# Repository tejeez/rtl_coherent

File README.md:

rtl_coherent: Synchronized RTL-SDR receivers
============================================

This is a hardware and software project to synchronize multiple RTL-SDR
receivers and make it possible to use them for applications such as
radio direction finding, passive radars, measuring equipment,
radio astronomy interferometers and MIMO communications.

Basic idea
----------

A single 28.8 MHz reference clock is distributed to all dongles. This makes
their sampling rates and local oscillator frequencies equal but doesn't
guarantee that they would actually sample simultaneously or that their
local oscillators would be in the same phase. 

Both the local oscillator phase and sample time offset get a random value
every time the dongles are initialized. This happens because commands don't
arrive to all receivers at exactly the same time and because their frequency
synthesizers are not known to provide a way to reset their phases.

To handle this we have to find the time and phase offsets every time the
receiver is used. This is done by disconnecting receivers from their antennas
and connecting them to a single white noise source. Cross correlating this
noise finds these offsets and lets us correct them. Currently the signal is
recorded in short blocks and each block starts with a burst of noise.

Electronics
-----------

The current hardware prototype has 3 dongles. One of them has the original
28.8 MHz crystal in place and other 2 dongles have the crystal removed. Clock
is distributed from one dongle to crystal pins of the two other dongles
through small capacitors. A better solution for a larger number of dongles
would be to have a separate 28.8 MHz oscillator and distribute it.

The inputs of the dongles are switched between antennas and noise source by
SA630D switches. They are controlled by an RC timing circuit triggered by
I2C clock in the dongles. Every time the R820T tuner chip receives a
command from the RTL2832U chip, there's some activity on the I2C bus.
This switches the inputs to the noise source and the timing circuit keeps
them there for some time after the I2C traffic has finished. The idea is to
have the noise burst triggered every time the center frequency is changed
which should make fast scanning easier.

A crude schematic of simple prototype hardware is now available in
[hardware/simple/](hardware/simple/README.md).

Software
--------

The current software is primarily written for radio direction finding based on
phase difference between elements of an antenna array.

The software records a block of signal from each dongle, cross correlates the
noise in beginning of each block to determine the phase and timing offsets,
corrects for them, divides the signal in narrow frequency bins using FFT and
calculates covariance between each receiver pair for each frequency bin.
Complex argument of an element in the covariance matrix represents the measured
phase difference between two antennas and is used for direction finding.
The same covariance matrix could also be used in more sophisticated direction
finding algorithms such as MUSIC or ESPRIT which might become more useful when
the number of antennas is increased.

rtl_coherent uses features in keenerd's experimental experimental RTL-SDR
branch. Get it from https://github.com/keenerd/rtl-sdr

The software has mostly been developed in Debian Linux on ordinary x86-64 PCs
but many other Linux distributions and architectures should work as well.

Experiments and demonstrations
------------------------------

Direction finding was first tested on 433 MHz amateur radio band using an array
of 3 groundplane antennas spaced by 1/3 wavelength.
See a video here: https://www.youtube.com/watch?v=8Wzb1mgZ0EE

It was also tested on higher HF bands using an array of ground mounted
vertical antennas. A spectrogram from 26.4 MHz to 28.8 MHz where color hue
represents the estimated angle of arrival can be seen here:
http://prkele.prk.tky.fi/~peltolt2/colordf_27600kHz_7h.jpg

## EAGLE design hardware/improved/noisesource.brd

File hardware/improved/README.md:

Schematics and PCB designs for parts of improved hardware.
PCBs have been designed using eagle.

noisesource.sch is the schematic for a better noise source based on three
BGA2803 MMICs. This MMIC was chosen because it has almost flat gain up to
2 GHz, works on 3.3 V and consumes relatively little current. Linearity
and noise figure are not important here.

noisesource.brd is a PCB design which has been built on a homemade PCB
and works. The positions of ground vias in the design don't exactly
correspond to what was built. Consider adding more vias near edge of the
board if you decide to order PCBs from somewhere.

The noise source hasn't been tested as a part of the coherent rtl-sdr setup
yet but it should work well and will be tested soon.

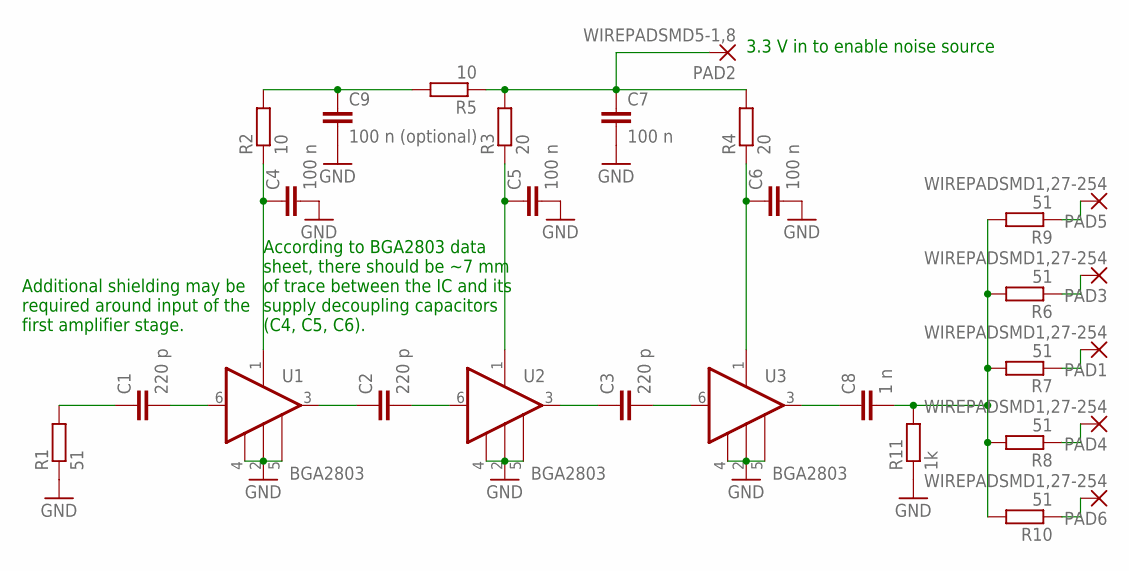
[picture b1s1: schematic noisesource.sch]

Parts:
C1, C2, C3: 220 p; C0805
C4, C5, C6, C7: 100 n; C0805
C8: 1 n; C0805
C9: 100 n (optional); C0805
PAD1, PAD3, PAD4, PAD5, PAD6: WIREPADSMD1,27-254; SMD1,27-2,54
PAD2: WIREPADSMD5-1,8; 5-1,8
R1, R6, R7, R8, R9, R10: 51; R0805
R2, R5: 10; R0805
R3, R4: 20; R0805
R11: 1k; R0805
U1, U2, U3: BGA2803; SOT363

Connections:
GND: C4.2, C5.2, C6.2, C7.2, C9.2, R1.1, R11.1, U1.2 (GND2), U1.4 (GND1), U1.5 (GND2), U2.2 (GND2), U2.4 (GND1), U2.5 (GND2), U3.2 (GND2), U3.4 (GND1), U3.5 (GND2)
unnamed: C2.1, U1.3 (OUT)
unnamed: C2.2, U2.6 (-IN)
unnamed: C3.1, U2.3 (OUT)
unnamed: C3.2, U3.6 (-IN)
unnamed: C1.1, R1.2
unnamed: C1.2, U1.6 (-IN)
unnamed: C4.1, R2.1, U1.1 (VCC)
unnamed: C5.1, R3.1, U2.1 (VCC)
unnamed: C6.1, R4.1, U3.1 (VCC)
unnamed: C7.1, PAD2.1, R3.2, R4.2, R5.1
unnamed: C8.1, U3.3 (OUT)
unnamed: PAD1.1, R7.1
unnamed: C9.1, R2.2, R5.2
unnamed: PAD3.1, R6.1
unnamed: PAD4.1, R8.1
unnamed: PAD5.1, R9.1
unnamed: PAD6.1, R10.1
unnamed: C8.2, R6.2, R7.2, R8.2, R9.2, R10.2, R11.2

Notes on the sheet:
3.3 V in to enable noise source
According to BGA2803 data sheet, there should be ~7 mm of trace between the IC and its supply decoupling capacitors (C4, C5, C6).
Additional shielding may be required around input of the first amplifier stage.

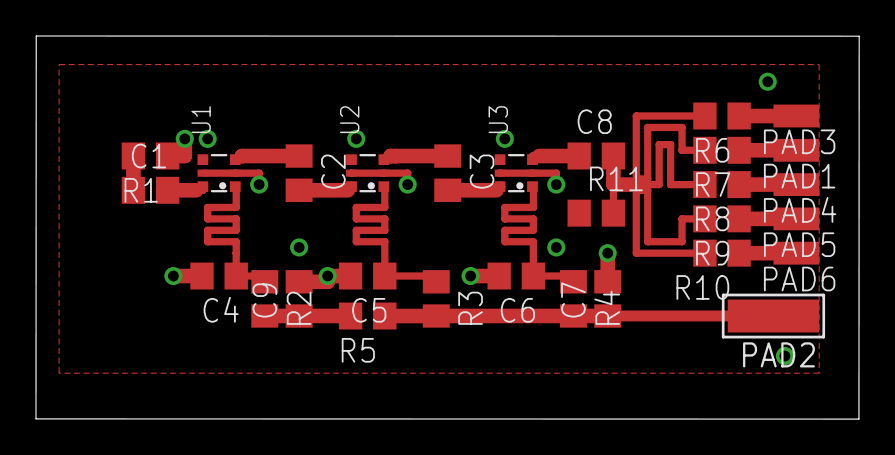
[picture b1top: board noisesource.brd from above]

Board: 2 copper layers, 45.7 x 21.3 mm, 29 parts (0 on the bottom side), 19 nets.

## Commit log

2015-06-10 Synchronous read from multiple dongles
2015-06-15 Fixed race condition and handling failed initializations
2015-06-15 Divide code in files
2015-06-15 Refucktoring
2015-06-15 Files
2015-06-18 Implement cross correlation in C
2015-06-20 Small fixes
2015-06-29 Implement switch control
2015-07-02 Calculate fractional sample delay
2015-07-10 Return pointers to synchronized signals
2015-07-11 Workaround for hardware problems etc
2015-07-17 something
2015-08-18 More error checking
2015-10-17 Print covariance matrix for testing
2015-10-18 Skip first samples for synchronization, change some pointer types
2015-10-20 Plot covariance matrix in python
2015-10-21 Fix phase correction
2015-10-21 Bigger plot
2015-10-22 Try to plot direction
2015-10-24 Make direction finding work
2015-10-24 Don't crash if a non-valid complex number is read from the pipe
2015-10-25 Added initial MUSIC DF implementation.
    It seems to be rather bad compared to the interferometer version...
2015-10-31 Bugfix in 'plot_covar.py': matplotlib calls updated, printing prettyfied
2015-10-31 Bugfix (the same as with 'plot_covar.py'): matplotlib calls
2015-12-30 Configuration file and cable skew correction
2016-01-02 Put DSP and dongle control in separate threads
2016-01-02 Implement direction finding in C and a waterfall display
2016-01-03 Improved waterfall
2016-04-28 Added red indicator line to sdl waterfall demo
2016-05-05 Read antenna positions from configuration file
2016-05-06 Implement persisent freq vs AOA scatterplot
2016-05-07 Add some documentation
2016-05-12 Added clean target to Makefile
2016-05-17 Added schematic
2016-05-17 Add a picture of hardware
2016-05-19 Added design for improved noise source
2016-05-25 Added calibration mode enabled by command line argument
2016-07-06 Added ambiguity simulation script
